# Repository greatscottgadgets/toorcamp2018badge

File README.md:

# Toorcamp 2018 Badge
This repository contains hardware designs and software for the ToorCamp 2018 badge, which is an electronic jar of fireflies. 

--------------------

# Documentation

Documentation for the ToorCamp 2018 Badge can be viewed on the Great Scott Gadgets [web page for this project](https://greatscottgadgets.com/toorcamp2018badge/).

--------------------

# Getting Help

We invite you to join our community discussions on [Discord](https://discord.gg/rsfMw3rsU8). Note that while technical support requests are welcome here, we do not have support staff on duty at all times.

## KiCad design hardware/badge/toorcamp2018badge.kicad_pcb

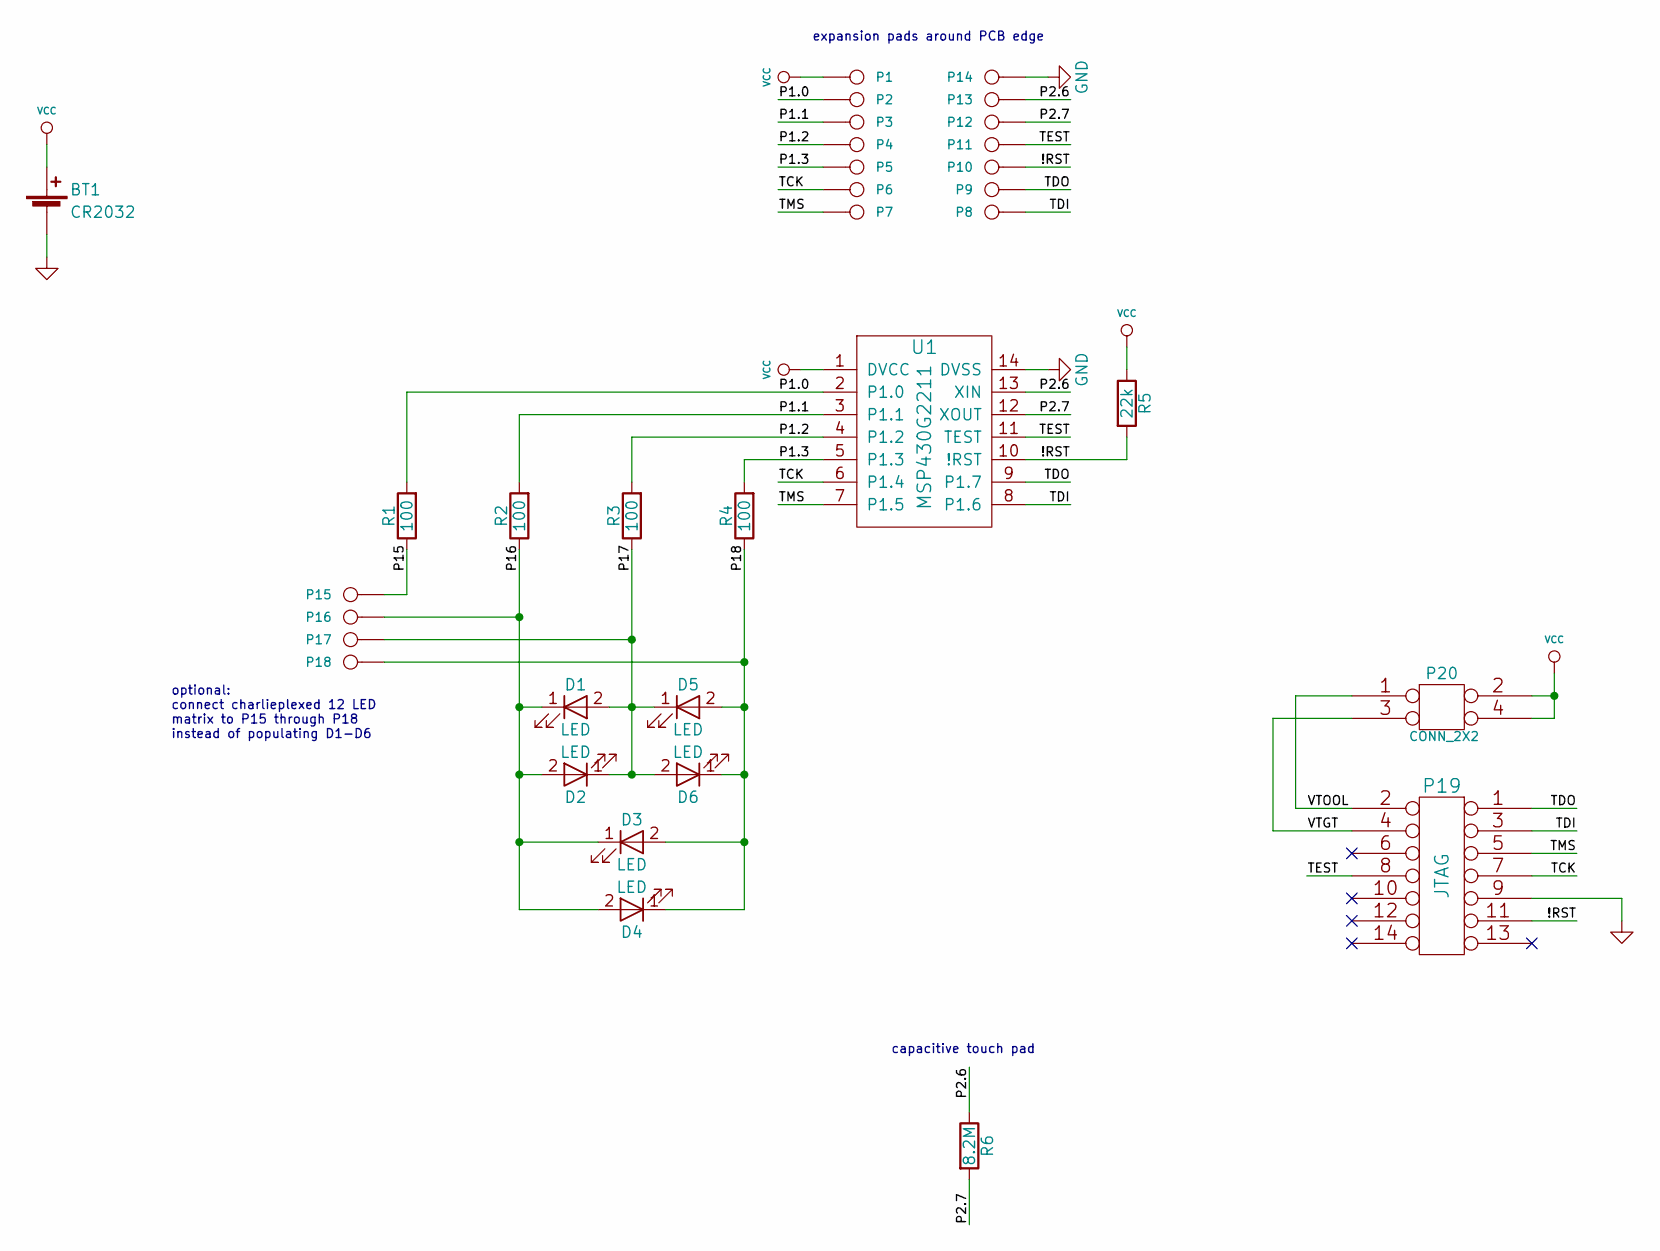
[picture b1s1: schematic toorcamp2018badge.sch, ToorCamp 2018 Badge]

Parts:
BT1: CR2032; BU2032SM-BT; Part Number BU2032SM-BT-GTR
D1, D2, D3, D4, D5, D6: LED; LED_D5.0mm; Part Number WP3A8GD
P1, P2, P3, P4, P5, P6, P7, P8, P9, P10, P11, P12, P13, P14: CONN_1; TESTPOINT-TOORCAMP-2018-EDGE
P15, P16, P17, P18: CONN_1; HEADER-1x1
P19: JTAG; HEADER-SMT-2x7
P20: CONN_2X2; HEADER-SMT-2x2
R1, R2, R3, R4: 100; RESISTOR-AXIAL-1.7x3.3mm; Part Number CFM14JT100R
R5: 22k; RESISTOR-AXIAL-2.3x6.0mm; Part Number CF14JT22K0
R6: 8.2M; RESISTOR-AXIAL-2.3x6.0mm; Part Number CF14JT8M20
U1: MSP430G2211; DIP14; Part Number MSP430G2211IN14

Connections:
/!RST: P10.1, P19.11, R5.2, U1.10 (!RST)
/P1.0: P2.1, R1.2, U1.2 (P1.0)
/P1.1: P3.1, R2.2, U1.3 (P1.1)
/P1.2: P4.1, R3.2, U1.4 (P1.2)
/P1.3: P5.1, R4.2, U1.5 (P1.3)
/P2.6: P13.1, R6.1, U1.13 (XIN)
/P2.7: P12.1, R6.2, U1.12 (XOUT)
/P15: P15.1, R1.1
/P16: D1.1 (K), D2.2 (A), D3.1 (K), D4.2 (A), P16.1, R2.1
/P17: D1.2 (A), D2.1 (K), D5.1 (K), D6.2 (A), P17.1, R3.1
/P18: D3.2 (A), D4.1 (K), D5.2 (A), D6.1 (K), P18.1, R4.1
/TCK: P6.1, P19.7, U1.6 (P1.4)
/TDI: P8.1, P19.3, U1.8 (P1.6)
/TDO: P9.1, P19.1, U1.9 (P1.7)
/TEST: P11.1, P19.8, U1.11 (TEST)
/TMS: P7.1, P19.5, U1.7 (P1.5)
/VTGT: P19.4, P20.3
/VTOOL: P19.2, P20.1
GND: BT1.2 (-), P14.1, P19.9, U1.14 (DVSS)
VCC: BT1.1 (+), P1.1, P20.2, P20.4, R5.1, U1.1 (DVCC)

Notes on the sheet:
optional: connect charlieplexed 12 LED matrix to P15 through P18 instead of populating D1-D6
expansion pads around PCB edge
capacitive touch pad

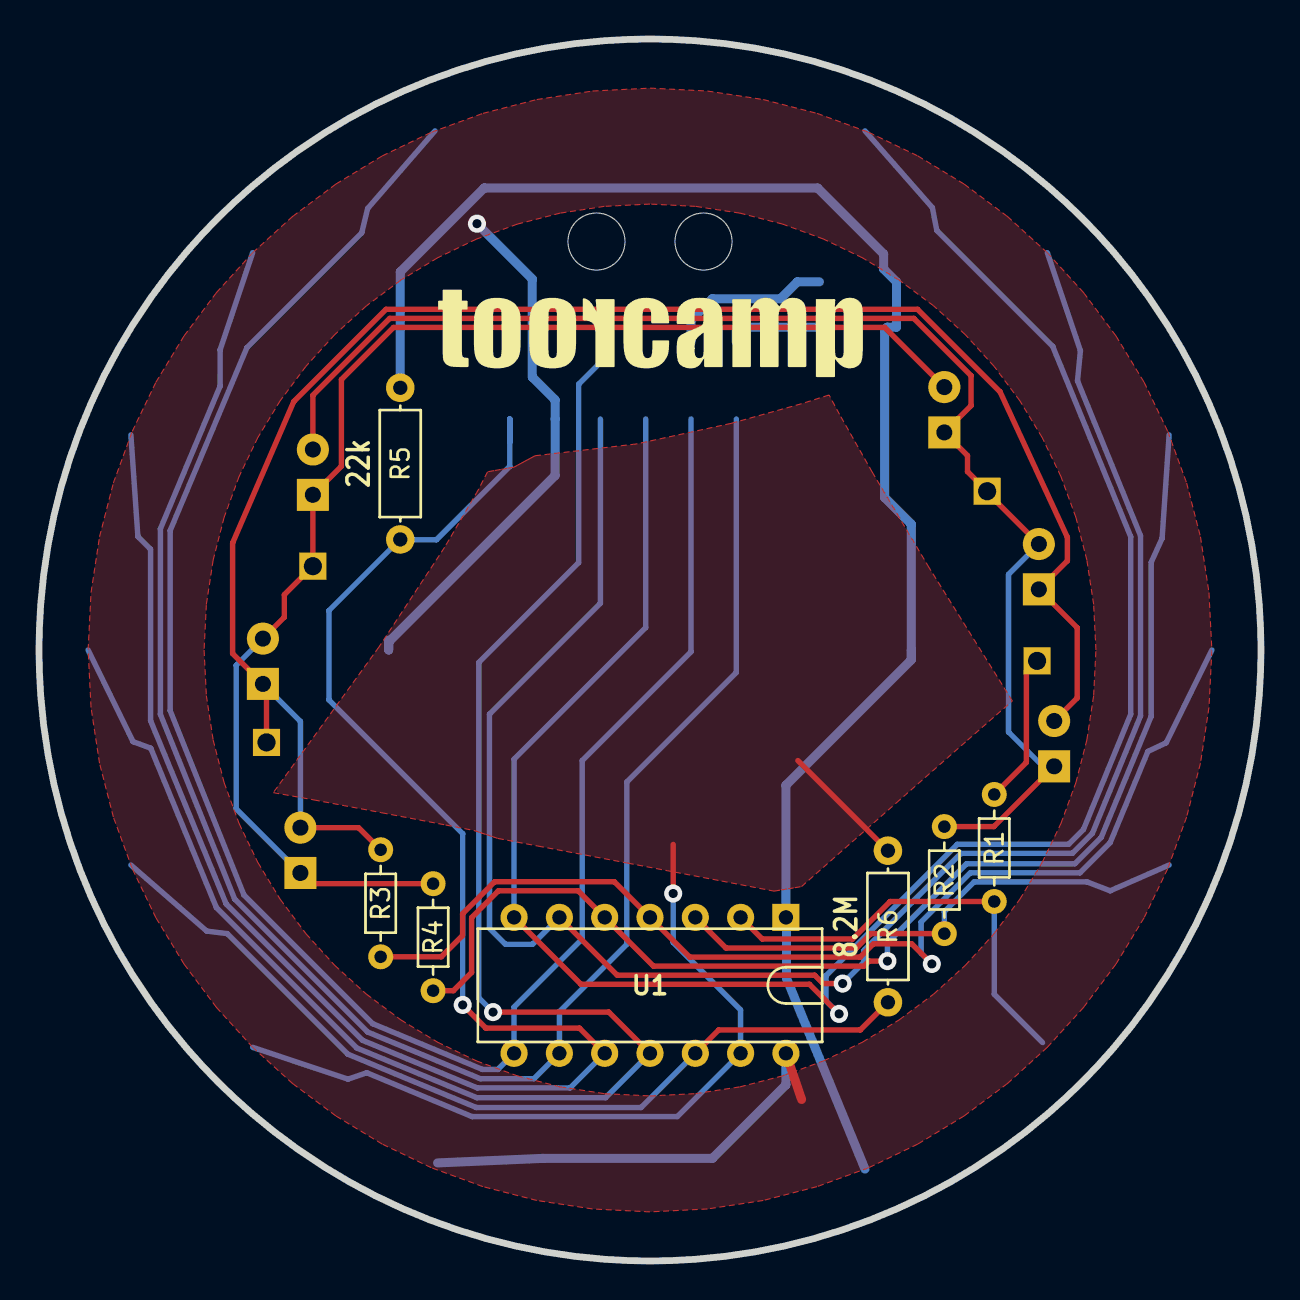
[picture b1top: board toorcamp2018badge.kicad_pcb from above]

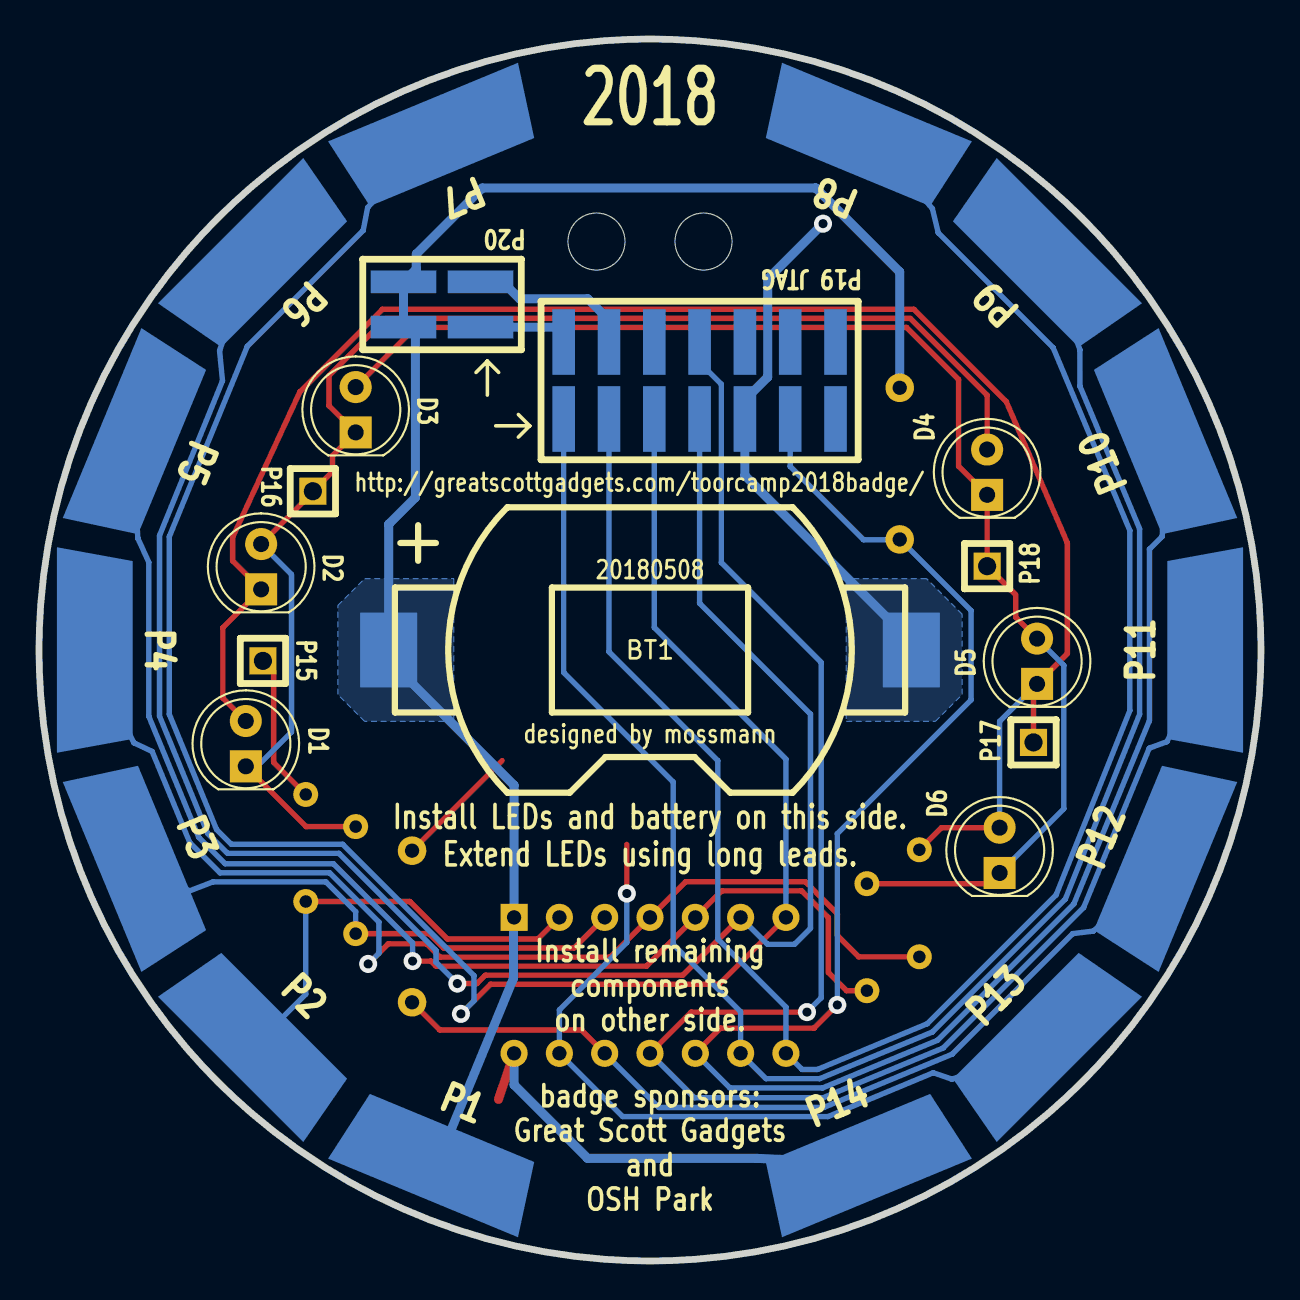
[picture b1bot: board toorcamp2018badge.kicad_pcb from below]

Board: 2 copper layers, 68.5 x 68.5 mm, 34 parts (27 on the bottom side), 20 nets.

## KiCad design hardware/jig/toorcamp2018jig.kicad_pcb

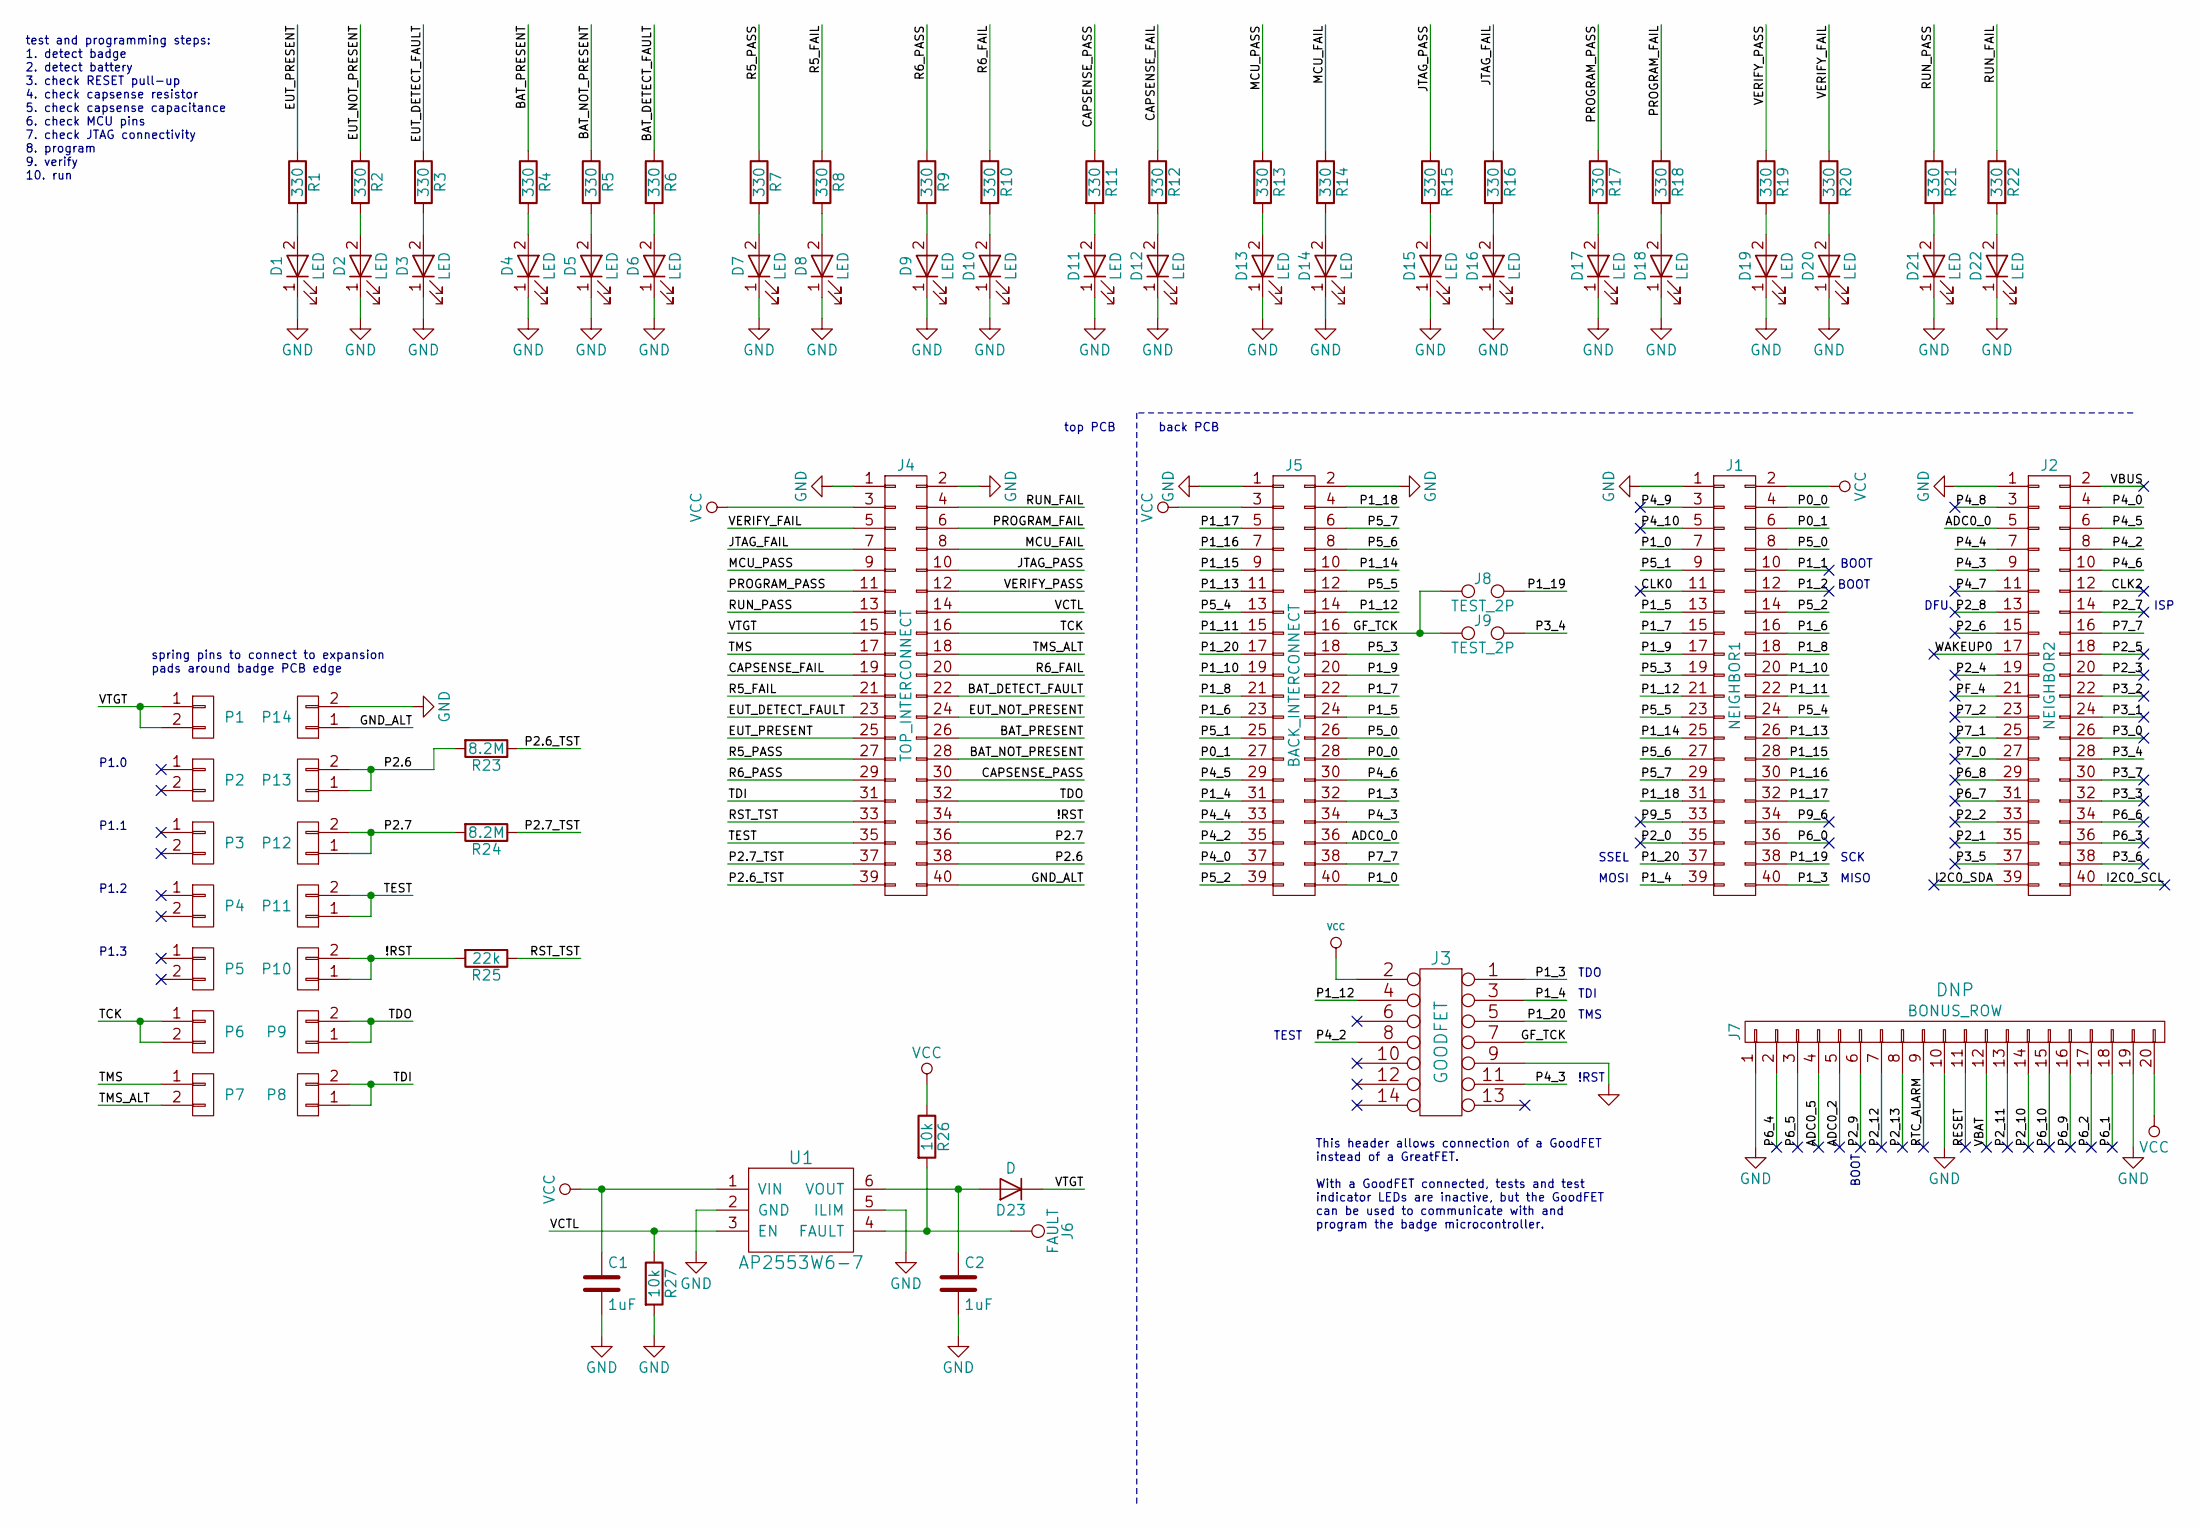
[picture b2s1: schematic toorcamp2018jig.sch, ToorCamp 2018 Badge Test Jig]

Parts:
C1, C2: 1uF; 0603; Part Number LMK107B7105KA-T
D1, D4, D5, D7, D9, D11, D13, D15, D17, D19, D21: LED; 0603D; Part Number SML-LX0603GW-TR
D2, D3, D6, D8, D10, D12, D14, D16, D18, D20, D22: LED; 0603D; Part Number SML-LX0603YW-TR
D23: D; SOD128; Part Number PMEG3050EP,115
J1: NEIGHBOR1; HEADER-2x20; Part Number PRPC020DAAN-RC
J2: NEIGHBOR2; HEADER-2x20; Part Number PRPC020DAAN-RC
J3: GOODFET; HEADER-2x7
J4: TOP_INTERCONNECT; HEADER-2x20; Part Number SSW-120-01-F-D
J5: BACK_INTERCONNECT; HEADER-2x20; Part Number PRPC020DBAN-M71RC
J6: FAULT; TESTPOINT-50MIL
J7: BONUS_ROW; HEADER-1x20; Part Number SSQ-120-23-G-S
J8, J9: TEST_2P; 0603-JUMPER
P1, P2, P3, P4, P5, P6, P7, P8, P9, P10, P11, P12, P13, P14: CONN_01X02; TESTPOINT-TOORCAMP-2018-JIG-SPRING; Part Number 009155002201006
R1, R2, R3, R4, R5, R6, R7, R8, R9, R10, R11, R12, R13, R14, R15, R16, R17, R18, R19, R20, R21, R22: 330; 0603; Part Number RMCF0603JT330R
R23, R24: 8.2M; 0603
R25: 22k; 0603; Part Number RC0603JR-0722KL
R26, R27: 10k; 0603; Part Number ERJ-3GEYJ103V
U1: AP2553W6-7; SOT457; Part Number AP2553W6-7

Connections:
/!RST: J4.34, P10.1, P10.2, R25.2
/ADC0_0: J2.5, J5.36
/ADC0_2: J7.5
/ADC0_5: J7.4
/BAT_DETECT_FAULT: J4.22, R6.1
/BAT_NOT_PRESENT: J4.28, R5.1
/BAT_PRESENT: J4.26, R4.1
/CAPSENSE_FAIL: J4.19, R12.1
/CAPSENSE_PASS: J4.30, R11.1
/CLK0: J1.11
/CLK2: J2.12
/EUT_DETECT_FAULT: J4.23, R3.1
/EUT_NOT_PRESENT: J4.24, R2.1
/EUT_PRESENT: J4.25, R1.1
/GF_TCK: J3.7, J5.16, J8.1, J9.1
/GND_ALT: J4.40, P14.1
/I2C0_SCL: J2.40
/I2C0_SDA: J2.39
/JTAG_FAIL: J4.7, R16.1
/JTAG_PASS: J4.10, R15.1
/MCU_FAIL: J4.8, R14.1
/MCU_PASS: J4.9, R13.1
/P0_0: J1.4, J5.28
/P0_1: J1.6, J5.27
/P1_0: J1.7, J5.40
/P1_1: J1.10
/P1_2: J1.12
/P1_3: J1.40, J3.1, J5.32
/P1_4: J1.39, J3.3, J5.31
/P1_5: J1.13, J5.24
/P1_6: J1.16, J5.23
/P1_7: J1.15, J5.22
/P1_8: J1.18, J5.21
/P1_9: J1.17, J5.20
/P1_10: J1.20, J5.19
/P1_11: J1.22, J5.15
/P1_12: J1.21, J3.4, J5.14
/P1_13: J1.26, J5.11
/P1_14: J1.25, J5.10
/P1_15: J1.28, J5.9
/P1_16: J1.30, J5.7
/P1_17: J1.32, J5.5
/P1_18: J1.31, J5.4
/P1_19: J1.38, J8.2
/P1_20: J1.37, J3.5, J5.17
/P2.6: J4.38, P13.1, P13.2, R23.2
/P2.6_TST: J4.39, R23.1
/P2.7: J4.36, P12.1, P12.2, R24.2
/P2.7_TST: J4.37, R24.1
/P2_0: J1.35
/P2_1: J2.35
/P2_2: J2.33
/P2_3: J2.20
/P2_4: J2.19
/P2_5: J2.18
/P2_6: J2.15
/P2_7: J2.14
/P2_8: J2.13
/P2_9: J7.6
/P2_10: J7.14
/P2_11: J7.13
/P2_12: J7.7
/P2_13: J7.8
/P3_0: J2.26
/P3_1: J2.24
/P3_2: J2.22
/P3_3: J2.32
/P3_4: J2.28, J9.2
/P3_5: J2.37
/P3_6: J2.38
/P3_7: J2.30
/P4_0: J2.4, J5.37
/P4_2: J2.8, J3.8, J5.35
/P4_3: J2.9, J3.11, J5.34
/P4_4: J2.7, J5.33
/P4_5: J2.6, J5.29
/P4_6: J2.10, J5.30
/P4_7: J2.11
/P4_8: J2.3
/P4_9: J1.3
/P4_10: J1.5
/P5_0: J1.8, J5.26
/P5_1: J1.9, J5.25
/P5_2: J1.14, J5.39
/P5_3: J1.19, J5.18
/P5_4: J1.24, J5.13
/P5_5: J1.23, J5.12
/P5_6: J1.27, J5.8
/P5_7: J1.29, J5.6
/P6_0: J1.36
/P6_1: J7.18
/P6_2: J7.17
/P6_3: J2.36
/P6_4: J7.2
/P6_5: J7.3
/P6_6: J2.34
/P6_7: J2.31
/P6_8: J2.29
/P6_9: J7.16
/P6_10: J7.15
/P7_0: J2.27
/P7_1: J2.25
/P7_2: J2.23
/P7_7: J2.16, J5.38
/P9_5: J1.33
/P9_6: J1.34
/PF_4: J2.21
/PROGRAM_FAIL: J4.6, R18.1
/PROGRAM_PASS: J4.11, R17.1
/R5_FAIL: J4.21, R8.1
/R5_PASS: J4.27, R7.1
/R6_FAIL: J4.20, R10.1
/R6_PASS: J4.29, R9.1
/RESET: J7.11
/RST_TST: J4.33, R25.1
/RTC_ALARM: J7.9
/RUN_FAIL: J4.4, R22.1
/RUN_PASS: J4.13, R21.1
/TCK: J4.16, P6.1, P6.2
/TDI: J4.31, P8.1, P8.2
/TDO: J4.32, P9.1, P9.2
/TEST: J4.35, P11.1, P11.2
/TMS: J4.17, P7.1
/TMS_ALT: J4.18, P7.2
/VBAT: J7.12
/VBUS: J2.2
/VCTL: J4.14, R27.1, U1.3 (EN)
/VERIFY_FAIL: J4.5, R20.1
/VERIFY_PASS: J4.12, R19.1
/VTGT: D23.1 (K), J4.15, P1.1, P1.2
/WAKEUP0: J2.17
GND: C1.2, C2.2, D1.1 (K), D2.1 (K), D3.1 (K), D4.1 (K), D5.1 (K), D6.1 (K), D7.1 (K), D8.1 (K), D9.1 (K), D10.1 (K), D11.1 (K), D12.1 (K), D13.1 (K), D14.1 (K), D15.1 (K), D16.1 (K), D17.1 (K), D18.1 (K), D19.1 (K), D20.1 (K), D21.1 (K), D22.1 (K), J1.1, J2.1, J3.9, J4.1, J4.2, J5.1, J5.2, J7.1, J7.10, J7.19, P14.2, R27.2, U1.2 (GND), U1.5 (ILIM)
unnamed: C2.1, D23.2 (A), U1.6 (VOUT)
unnamed: D1.2 (A), R1.2
unnamed: D2.2 (A), R2.2
unnamed: D3.2 (A), R3.2
unnamed: D4.2 (A), R4.2
unnamed: D5.2 (A), R5.2
unnamed: D6.2 (A), R6.2
unnamed: D7.2 (A), R7.2
unnamed: D8.2 (A), R8.2
unnamed: D9.2 (A), R9.2
unnamed: D10.2 (A), R10.2
unnamed: D11.2 (A), R11.2
unnamed: D12.2 (A), R12.2
unnamed: D13.2 (A), R13.2
unnamed: D14.2 (A), R14.2
unnamed: D15.2 (A), R15.2
unnamed: D16.2 (A), R16.2
unnamed: D17.2 (A), R17.2
unnamed: D18.2 (A), R18.2
unnamed: D19.2 (A), R19.2
unnamed: D20.2 (A), R20.2
unnamed: D21.2 (A), R21.2
unnamed: D22.2 (A), R22.2
unnamed: J6.1, R26.2, U1.4 (FAULT)
VCC: C1.1, J1.2, J3.2, J4.3, J5.3, J7.20, R26.1, U1.1 (VIN)

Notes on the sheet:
spring pins to connect to expansion pads around badge PCB edge
This header allows connection of a GoodFET instead of a GreatFET. With a GoodFET connected, tests and test indicator LEDs are inactive, but the GoodFET can be used to communicate with and program the badge microcontroller.
test and programming steps: 1. detect badge 2. detect battery 3. check RESET pull-up 4. check capsense resistor 5. check capsense capacitance 6. check MCU pins 7. check JTAG connectivity 8. program 9. verify 10. run
MISO
MOSI
SCK
SSEL
ISP
DFU
BOOT
!RST
TDO
TDI
TMS
TEST
top PCB
back PCB
P1.0
P1.1
P1.2
P1.3

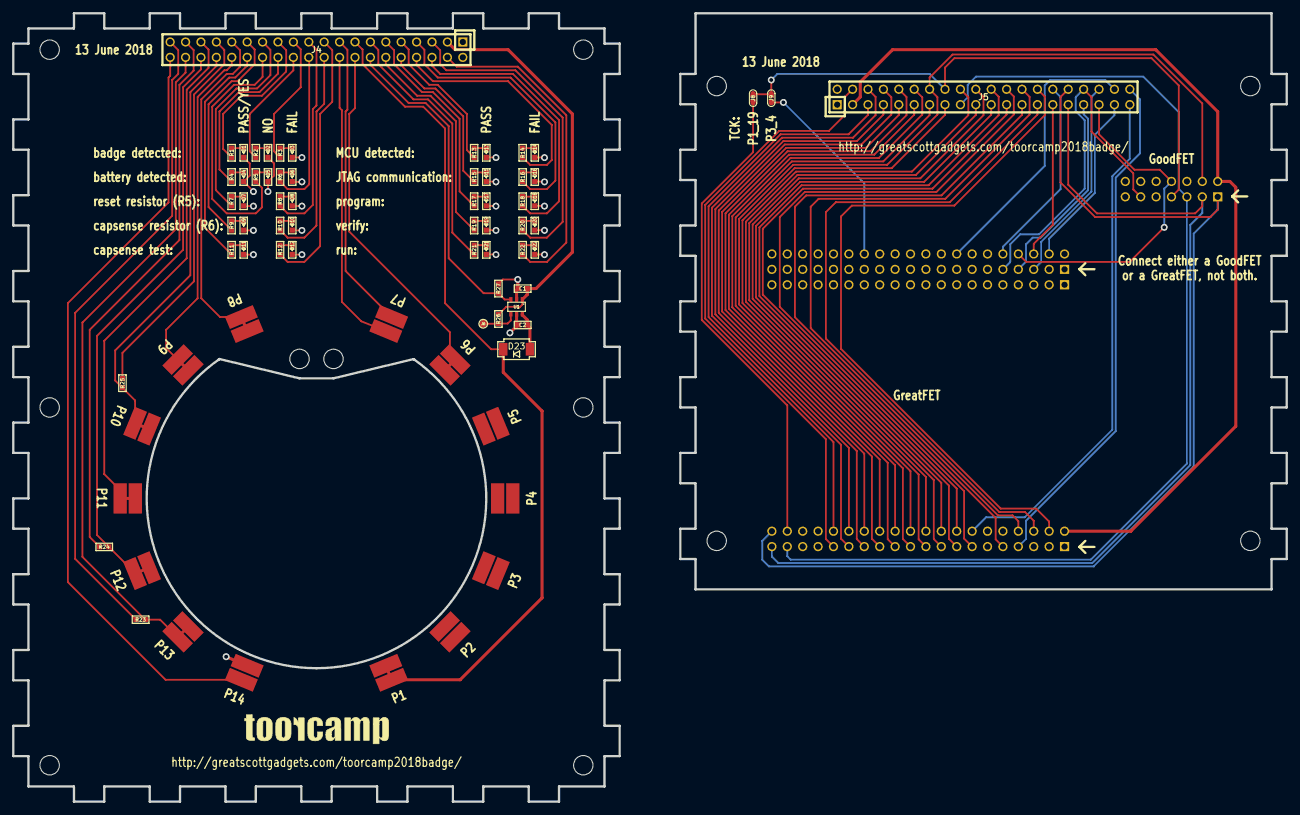
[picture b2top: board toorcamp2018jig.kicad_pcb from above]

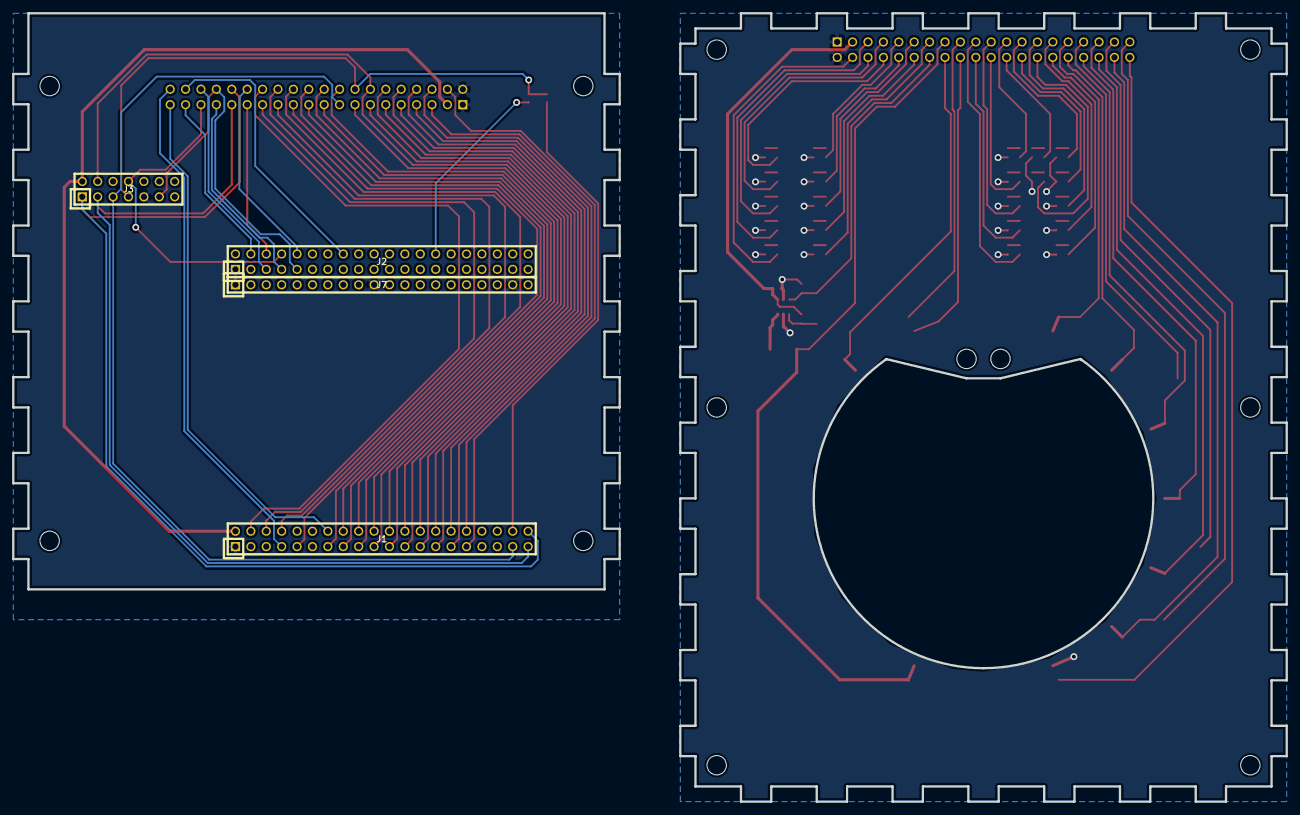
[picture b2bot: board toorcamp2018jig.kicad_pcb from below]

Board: 2 copper layers, 100.0 x 130.0 mm, 76 parts (4 on the bottom side), 102 nets.

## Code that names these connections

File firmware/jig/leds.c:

/*
 * This file is part of GreatFET (ish)
 */

#include <libopencm3/lpc43xx/scu.h>
#include <gpio_lpc.h>
#include "leds.h"
#include "tests.h"

static struct gpio_t eut_present = GPIO(2, 10);
static struct gpio_t eut_not_present = GPIO(1, 8);
static struct gpio_t eut_detect_fault = GPIO(1, 9);
detect_t badge_leds = {
	.present = &eut_present,
	.not_present = &eut_not_present,
	.fault = &eut_detect_fault,
};

static struct gpio_t bat_present = GPIO(2, 9);
static struct gpio_t bat_not_present = GPIO(0, 0);
static struct gpio_t bat_detect_fault = GPIO(1, 0);
detect_t battery_leds = {
	.present = &bat_present,
	.not_present = &bat_not_present,
	.fault = &bat_detect_fault,
};

static struct gpio_t r5_pass = GPIO(0, 1);
static struct gpio_t r5_fail = GPIO(1, 1);
test_t r5_leds = {
	.pass = &r5_pass,
	.fail = &r5_fail,
};

static struct gpio_t r6_pass = GPIO(2, 5);
static struct gpio_t r6_fail = GPIO(1, 2);
test_t r6_leds = {
	.pass = &r6_pass,
	.fail = &r6_fail,
};

static struct gpio_t mcu_pass = GPIO(0, 2);
static struct gpio_t mcu_fail = GPIO(2, 15);
test_t mcu_leds = {
	.pass = &mcu_pass,
	.fail = &mcu_fail,
};

static struct gpio_t capsense_pass = GPIO(2, 6);
static struct gpio_t capsense_fail = GPIO(1, 3);
test_t capsense_leds = {
	.pass = &capsense_pass,
	.fail = &capsense_fail,
};

static struct gpio_t jtag_pass = GPIO(1, 7);
static struct gpio_t jtag_fail = GPIO(0, 3);
test_t jtag_leds = {
	.pass = &jtag_pass,
	.fail = &jtag_fail,
};

static struct gpio_t program_pass = GPIO(1, 6);
static struct gpio_t program_fail = GPIO(2, 7);
test_t program_leds = {
	.pass = &program_pass,
	.fail = &program_fail,
};

static struct gpio_t verify_pass = GPIO(2, 14);
static struct gpio_t verify_fail = GPIO(0, 12);
test_t verify_leds = {
	.pass = &verify_pass,
	.fail = &verify_fail,
};

static struct gpio_t run_pass = GPIO(2, 13);
static struct gpio_t run_fail = GPIO(0, 13);
test_t run_leds = {
	.pass = &run_pass,
	.fail = &run_fail,
};

#define EUT_PRESENT (P5_1)
#define EUT_NOT_PRESENT (P1_5)
#define EUT_DETECT_FAULT (P1_6)

#define BAT_PRESENT (P5_0)
#define BAT_NOT_PRESENT (P0_0)
#define BAT_DETECT_FAULT (P1_7)

#define R5_PASS (P0_1)
#define R5_FAIL (P1_8)
#define R6_PASS (P4_5)
#define R6_FAIL (P1_9)

#define MCU_PASS (P1_15)
#define MCU_FAIL (P5_6)

#define CAPSENSE_PASS (P4_6)
#define CAPSENSE_FAIL (P1_10)

#define JTAG_PASS (P1_14)
#define JTAG_FAIL (P1_16)

#define PROGRAM_PASS (P1_13)
#define PROGRAM_FAIL (P5_7)

#define VERIFY_PASS (P5_5)
#define VERIFY_FAIL (P1_17)

#define RUN_PASS (P5_4)
#define RUN_FAIL (P1_18)

// Luckily all are pinmux function 0
#define GPIO_MODE SCU_GPIO_FAST | SCU_GPIO_PUP | SCU_CONF_FUNCTION0


void show_detect_result(uint8_t result, detect_t detect) {
    switch(result) {
        case PASS:
            gpio_write(detect.present, 1);
            gpio_write(detect.not_present, 0);
            gpio_write(detect.fault, 0);
            break;
        case FAIL:
            gpio_write(detect.present, 0);
            gpio_write(detect.not_present, 1);
            gpio_write(detect.fault, 0);
            break;
        case FAULT:
            gpio_write(detect.present, 0);
            gpio_write(detect.not_present, 0);
            gpio_write(detect.fault, 1);
            break;
        case CLEAR:
            gpio_write(detect.present, 0);
            gpio_write(detect.not_present, 0);
            gpio_write(detect.fault, 0);
            break;
        case ALL:
            gpio_write(detect.present, 1);
            gpio_write(detect.not_present, 1);
            gpio_write(detect.fault, 1);
            break;
    }
}

void show_test_result(uint8_t result, test_t test) {
    switch(result) {
        case PASS:
            gpio_write(test.pass, 1);
            gpio_write(test.fail, 0);
            break;
        case FAIL:
            gpio_write(test.pass, 0);
            gpio_write(test.fail, 1);
            break;
        case CLEAR:
            gpio_write(test.pass, 0);
            gpio_write(test.fail, 0);
            break;
        case ALL:
            gpio_write(test.pass, 1);
            gpio_write(test.fail, 1);
            break;
    }
}

void init_leds(void) {
	scu_pinmux(EUT_PRESENT, GPIO_MODE);
	scu_pinmux(EUT_NOT_PRESENT, GPIO_MODE);
	scu_pinmux(EUT_DETECT_FAULT, GPIO_MODE);

	scu_pinmux(BAT_PRESENT, GPIO_MODE);
	scu_pinmux(BAT_NOT_PRESENT, GPIO_MODE);
	scu_pinmux(BAT_DETECT_FAULT, GPIO_MODE);

	scu_pinmux(R5_PASS, GPIO_MODE);
	scu_pinmux(R5_FAIL, GPIO_MODE);
	scu_pinmux(R6_PASS, GPIO_MODE);
	scu_pinmux(R6_FAIL, GPIO_MODE);

	scu_pinmux(MCU_PASS, GPIO_MODE);
	scu_pinmux(MCU_FAIL, GPIO_MODE);

	scu_pinmux(CAPSENSE_PASS, GPIO_MODE);
	scu_pinmux(CAPSENSE_FAIL, GPIO_MODE);

	scu_pinmux(JTAG_PASS, GPIO_MODE);
	scu_pinmux(JTAG_FAIL, GPIO_MODE);

	scu_pinmux(PROGRAM_PASS, GPIO_MODE);
	scu_pinmux(PROGRAM_FAIL, GPIO_MODE);

	scu_pinmux(VERIFY_PASS, GPIO_MODE);
	scu_pinmux(VERIFY_FAIL, GPIO_MODE);

	scu_pinmux(RUN_PASS, GPIO_MODE);
	scu_pinmux(RUN_FAIL, GPIO_MODE);

	gpio_output(&eut_present);
	gpio_output(&eut_not_present);
	gpio_output(&eut_detect_fault);
	gpio_output(&bat_present);
	gpio_output(&bat_not_present);
	gpio_output(&bat_detect_fault);
	gpio_output(&r5_pass);
	gpio_output(&r5_fail);
	gpio_output(&r6_pass);
	gpio_output(&r6_fail);
	gpio_output(&mcu_pass);
	gpio_output(&mcu_fail);
	gpio_output(&capsense_pass);
	gpio_output(&capsense_fail);
	gpio_output(&jtag_pass);
	gpio_output(&jtag_fail);
	gpio_output(&program_pass);
	gpio_output(&program_fail);
	gpio_output(&verify_pass);
	gpio_output(&verify_fail);
	gpio_output(&run_pass);
	gpio_output(&run_fail);
}

void clear_leds(void) {
	show_detect_result(CLEAR, badge_leds);
	show_detect_result(CLEAR, battery_leds);

	show_test_result(CLEAR, r5_leds);
	show_test_result(CLEAR, r6_leds);
	show_test_result(CLEAR, mcu_leds);
	show_test_result(CLEAR, capsense_leds);
	show_test_result(CLEAR, jtag_leds);
	show_test_result(CLEAR, program_leds);
	show_test_result(CLEAR, verify_leds);
	show_test_result(CLEAR, run_leds);
}

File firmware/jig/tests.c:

/*
 * This file is part of GreatFET (ish)
 */

#include <libopencm3/lpc43xx/adc.h>
#include <libopencm3/lpc43xx/scu.h>
#include <gpio_lpc.h>

#include <jtag430.h>
#include <jtag.h>

#include"tests.h"
#include "badge_firmware.h"
#include"leds.h"


static struct gpio_t r5_adc = GPIO(3, 15);
static struct gpio_t r5_sply = GPIO(2, 11);
static struct gpio_t r6_sply = GPIO(2, 0);
static struct gpio_t gnd_alt = GPIO(0, 4);
// static struct gpio_t tms = GPIO(0, 15);
static struct gpio_t tms_alt = GPIO(2, 12);
static struct gpio_t vctl = GPIO(1, 5);
static struct gpio_t vtgt = GPIO(1, 4);


#define R5_ADC (P7_7) // GPIO3[15]
#define R6_ADC (ADC0) // This isn't used, mostly a comment
#define R5_SPLY (P5_2) // GPIO2[11]
#define R6_SPLY (P4_0) // GPIO2[0]
#define GND_ALT (P1_0) // GPIO0[4]
#define TMS (P1_20) // GPIO0[15]
#define TMS_ALT (P5_3) // GPIO2[12]
#define VCTL (P1_12) // GPIO1[5]
#define VTGT (P1_11) // GPIO1[4]

// Luckily all are pinmux function 0
#define GPIO_MODE SCU_GPIO_FAST | SCU_GPIO_PUP | SCU_CONF_FUNCTION0

// Initialise the pins for EUT/BAT detect and R5/E6 check
void init_tests(void) {
	scu_pinmux(R5_ADC, GPIO_MODE);
	scu_pinmux(R5_SPLY, GPIO_MODE);
	scu_pinmux(R6_SPLY, GPIO_MODE);
	scu_pinmux(GND_ALT, GPIO_MODE);
	scu_pinmux(TMS, GPIO_MODE);
	scu_pinmux(TMS_ALT, SCU_GPIO_FAST | SCU_GPIO_PDN | SCU_CONF_FUNCTION0);
	scu_pinmux(VCTL, GPIO_MODE);
	scu_pinmux(VTGT, SCU_GPIO_FAST | SCU_GPIO_PDN | SCU_CONF_FUNCTION0);
    gpio_input(&r5_adc);
    gpio_output(&r5_sply);
    gpio_write(&r5_sply, 0);
    gpio_output(&r6_sply);
    gpio_write(&r5_sply, 0);
    gpio_input(&gnd_alt);
    gpio_input(&tms_alt);
    gpio_output(&vctl);
    gpio_write(&vctl, 0);
    gpio_input(&vtgt);
	gpio_output(&tms);
}

uint8_t badge_detect() {
	uint8_t p7, p14, result = FAIL;
    p14 = gpio_read(&gnd_alt);
    gpio_write(&tms, 1);
    p7 = gpio_read(&tms_alt);
    if((p7 == 1) && (p14 == 0)) {
        delay_us(500000);
        if((p7 == 1) && (p14 == 0))
            result = PASS;
    }
    show_detect_result(result, badge_leds);
    gpio_write(&tms, 0);
	return result;
}

uint8_t battery_detect() {
	uint8_t result = FAULT;
    gpio_write(&vctl, 0);
    delay_us(10000000);
    if(gpio_read(&vtgt)) {
        result = PASS;
    } else {
        gpio_write(&vctl, 1);
        delay_us(10000);
        if(gpio_read(&vtgt)) {
            result = FAIL;
        }
    }
    show_detect_result(result, battery_leds);
	return result;
}

// This is Dominic trying to narrow down the values for R5
// These values need to be fixed
#define R5_HIGH 0x60
#define R5_LOW 0x30

uint8_t r5_test() {
    uint8_t pins = 1<<6;
	uint8_t clkdiv = 45;
	uint8_t clks = 0x2;
    uint8_t result = FAIL;
	uint16_t value;
    gpio_write(&r5_sply, 1);

    ADC0_CR = ADC_CR_SEL((uint32_t) pins) |
    ADC_CR_CLKDIV((uint32_t) clkdiv) |
    ADC_CR_CLKS((uint32_t) clks) |
    ADC_CR_PDN;
    ADC0_CR |= ADC_CR_START(1);

    while(!(ADC0_DR6 & ADC_DR_DONE));
    value = (ADC0_DR6>>6) & 0x3ff;

    if((value >= R5_LOW) && (value <= R5_HIGH))
        result = PASS;

    gpio_write(&r5_sply, 0);
    show_test_result(result, r5_leds);
	return result;
}

// This is Dominic trying to narrow down the values for R6
// These values need to be fixed
#define R6_HIGH 0x60
#define R6_LOW 0x30

uint8_t r6_test() {
    uint8_t pins = 1;
	uint8_t clkdiv = 45;
	uint8_t clks = 0x2;
    uint8_t result = FAIL;
	uint16_t value;
    gpio_write(&r6_sply, 1);

    ADC0_CR = ADC_CR_SEL((uint32_t) pins) |
    ADC_CR_CLKDIV((uint32_t) clkdiv) |
    ADC_CR_CLKS((uint32_t) clks) |
    ADC_CR_PDN;
    ADC0_CR |= ADC_CR_START(1);

    while(!(ADC0_DR0 & ADC_DR_DONE));
    value = (ADC0_DR0>>6) & 0x3ff;

    if((value >= R6_LOW) && (value <= R6_HIGH))
        result = PASS;

    gpio_write(&r6_sply, 0);
    show_test_result(result, r6_leds);
	return result;
}

// Not implemented
uint8_t mcu_test() {
	uint8_t result = PASS;
    show_test_result(result, mcu_leds);
	return result;
}

// Not implemented
uint8_t capsense_test() {
	uint8_t result = PASS;
    show_test_result(result, capsense_leds);
	return result;
}

uint8_t jtag_test() {
    uint8_t result = FAIL;
	jtag_setup();
	uint8_t jtagid = jtag430_start_reset_halt();
	if(jtagid != 0x89) {
		// Try a second time
		jtagid = jtag430_start_reset_halt();
	}
	if(jtagid == 0x89) {
		result = PASS;
	}
    show_test_result(result, jtag_leds);
	return result;
}

uint8_t program() {
    uint8_t result = FAIL;
	// ERASE MSP430 flash
	// These values are taken from GoodFET jtag430.c
	jtag430_eraseflash(0xA506,0xFFFE,0x3000,0);

	// Write firmware
	uint16_t *buffer = (uint16_t*) badge_firmware;
	jtag430_writeflash_bulk(0xF800, badge_firmware_len/2, buffer);
    result = PASS;
    show_test_result(result, program_leds);
	return result;
}

uint8_t verify() {
	uint8_t result = PASS;
    uint16_t *buffer = (uint16_t*) badge_firmware;
    uint16_t i;
    for(i = 0; i < badge_firmware_len/2; i++) {
        if(jtag430_readmem(0xF800+(i*2)) != buffer[i]) {
            result = FAIL;
            break;
        }
    }
    show_test_result(result, verify_leds);
	return result;
}

uint8_t run() {
	// Put in to RUN mode
	jtag430_stop();
	// I don't really know how we detect success or failure here
	// So we'll succeed for now
	uint8_t result = PASS;
    show_test_result(result, run_leds);
	return result;
}

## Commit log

2018-05-09 ToorCamp 2018 badge hardware design
2018-05-09 removed ToorCamp logos and event information
2018-05-09 added Great Scott Gadgets gear logo
2018-05-09 removed lanyard holes
2018-06-05 moved badge design to subdirectory
2018-06-13 ToorCamp 2018 badge test jig hardware design
2018-06-13 added paste layer for spring pins
2018-06-14 Boiler plate for out of tree GreatFET firmware
2018-06-17 added laser cut acrylic enclosure for test jig
2018-06-18 filled in test jig bom info
2018-06-19 LEDs and firmware writing functionality
2018-06-19 Separate out LED twiddling and test running
2018-06-19 Add functions to display detect status
2018-06-20 Configure GPIO pins for tests
2018-06-20 First attempt at ADC function for R5 and R6 testing
2018-06-20 Add some outline code for verify function
2018-06-20 Tweak R5 & R6 tests
2018-06-20 Add some logic to badge test / flash process
2018-06-20 Add some logic to badge flash/test state machine
2018-06-20 badge firmware
2018-06-21 Fix badge detect test reliability
2018-06-30 Revealed source code for "party mode" Easter egg. This is the revision that was used to flash badges at ToorCamp 2018. Congratulations to Gareth for discovering how the Easter egg is activated!
2018-09-13 Include badge firmware in test jig firmware
2019-06-19 update metadata
2019-06-19 add instructions for flashing with GreatFET
2022-12-06 Documentation: Add BOM and picture to repository. Update Read Me

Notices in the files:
hardware/badge/toorcamp2018badge.kicad_pcb:
Copyright 2018 Great Scott Gadgets
License: BSD-3-Clause, http://greatscottgadgets.com/toorcamp2018badge
